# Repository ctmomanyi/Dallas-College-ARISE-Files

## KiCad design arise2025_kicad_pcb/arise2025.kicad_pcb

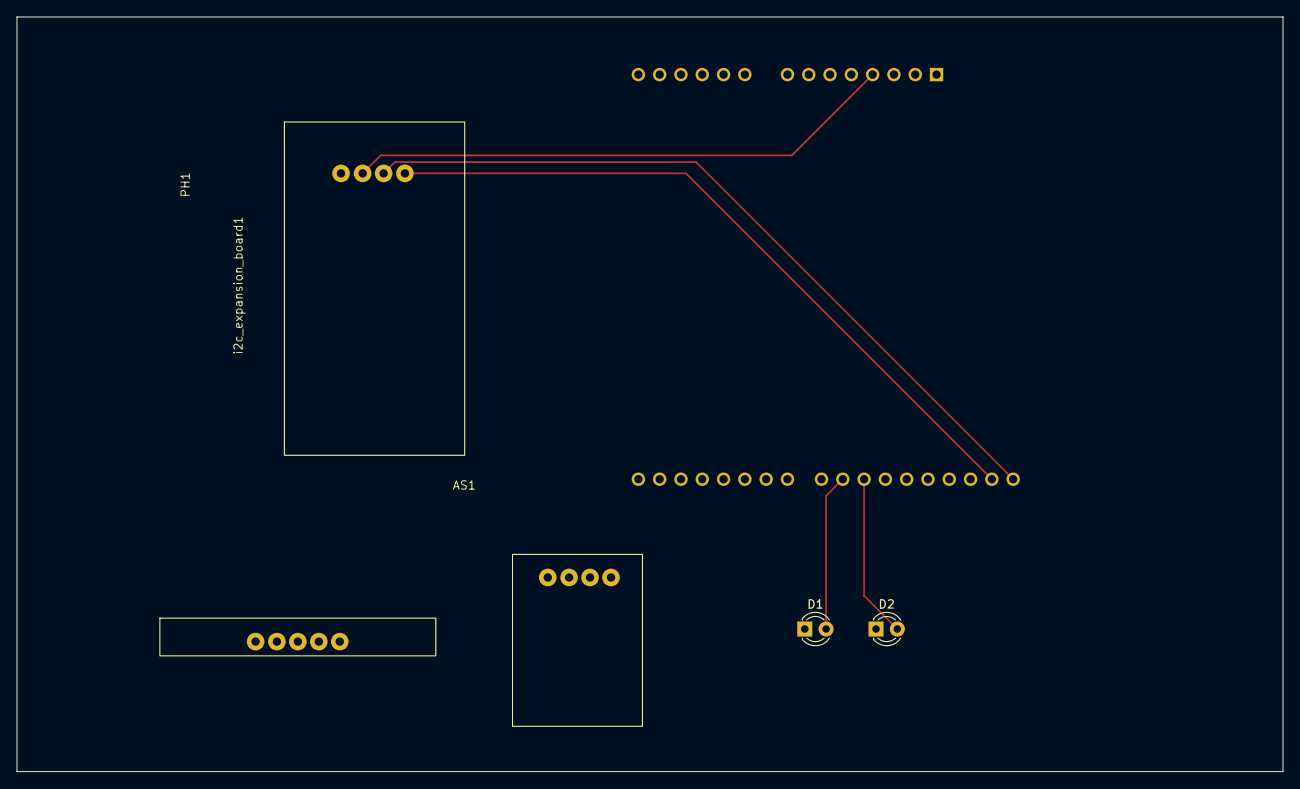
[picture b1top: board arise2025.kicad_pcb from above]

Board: 2 copper layers, 151.0 x 90.0 mm, 6 parts (1 on the bottom side), 6 nets.

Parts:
A1: Arduino_UNO_R3
AS1: as7341
D1, D2: LED; LED_D3.0mm
PH1: atlasPHboard
i2c_expansion_board1: i2c expansion board

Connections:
GND: A1.6 (GND), i2c_expansion_board1.1 (GND)
unnamed: A1.4 (3V3), i2c_expansion_board1.2 (VCC)
unnamed: A1.24 (D9), D1.2 (A)
unnamed: A1.25 (D10), D2.2 (A)
unnamed: A1.32 (SCL/A5), i2c_expansion_board1.3 (SCL)
unnamed: A1.31 (SDA/A4), i2c_expansion_board1.4 (SDA)

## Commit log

2025-12-02 Dallas College ARISE Files
    These are the files I used to create my prototype in the Dallas College ARISE Undergraduate Research Program.
